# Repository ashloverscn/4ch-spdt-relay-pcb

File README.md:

# 4ch-spdt-relay-pcb
4ch-spdt-relay-pcb

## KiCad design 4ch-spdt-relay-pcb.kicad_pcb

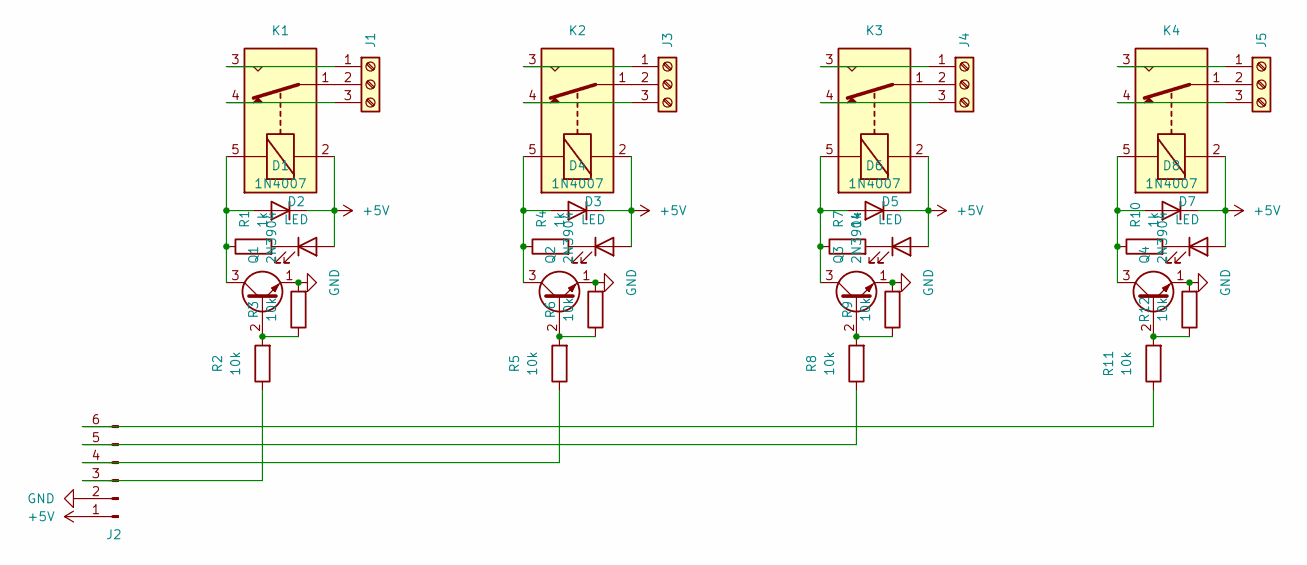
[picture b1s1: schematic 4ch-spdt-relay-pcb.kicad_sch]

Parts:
D1, D4, D6, D8: 1N4007; D_DO-41_SOD81_P10.16mm_Horizontal
D2, D3, D5, D7: LED; LED_D5.0mm
J1, J3, J4, J5: Screw_Terminal_01x03; TerminalBlock_Phoenix_MKDS-1,5-3-5.08_1x03_P5.08mm_Horizont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
J2: Conn_01x06_Pin; PinHeader_1x06_P2.54mm_Vertical
K1, K2, K3, K4: G5LE-1; Relay_SPDT_Omron-G5LE-1
Q1, Q2, Q3, Q4: 2N3904; TO-92_Inline
R1, R4, R7, R10: 1k; R_Axial_DIN0204_L3.6mm_D1.6mm_P2.54mm_Vertical
R2, R3, R5, R6, R8, R9, R11, R12: 10k; R_Axial_DIN0204_L3.6mm_D1.6mm_P2.54mm_Vertical

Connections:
+5V: D1.1 (K), D2.2 (A), D3.2 (A), D4.1 (K), D5.2 (A), D6.1 (K), D7.2 (A), D8.1 (K), J2.1, K1.2, K2.2, K3.2, K4.2
GND: J2.2, Q1.1 (E), Q2.1 (E), Q3.1 (E), Q4.1 (E), R3.2, R6.2, R9.2, R12.2
unnamed: D1.2 (A), K1.5, Q1.3 (C), R1.1
unnamed: D2.1 (K), R1.2
unnamed: D3.1 (K), R4.2
unnamed: D4.2 (A), K2.5, Q2.3 (C), R4.1
unnamed: D5.1 (K), R7.2
unnamed: D6.2 (A), K3.5, Q3.3 (C), R7.1
unnamed: D7.1 (K), R10.2
unnamed: D8.2 (A), K4.5, Q4.3 (C), R10.1
unnamed: J1.1, K1.3
unnamed: J1.2, K1.1
unnamed: J1.3, K1.4
unnamed: J2.3, R2.1
unnamed: J2.4, R5.1
unnamed: J2.5, R8.1
unnamed: J2.6, R11.1
unnamed: J3.1, K2.3
unnamed: J3.2, K2.1
unnamed: J3.3, K2.4
unnamed: J4.1, K3.3
unnamed: J4.2, K3.1
unnamed: J4.3, K3.4
unnamed: J5.1, K4.3
unnamed: J5.2, K4.1
unnamed: J5.3, K4.4
unnamed: Q1.2 (B), R2.2, R3.1
unnamed: Q2.2 (B), R5.2, R6.1
unnamed: Q3.2 (B), R8.2, R9.1
unnamed: Q4.2 (B), R11.2, R12.1

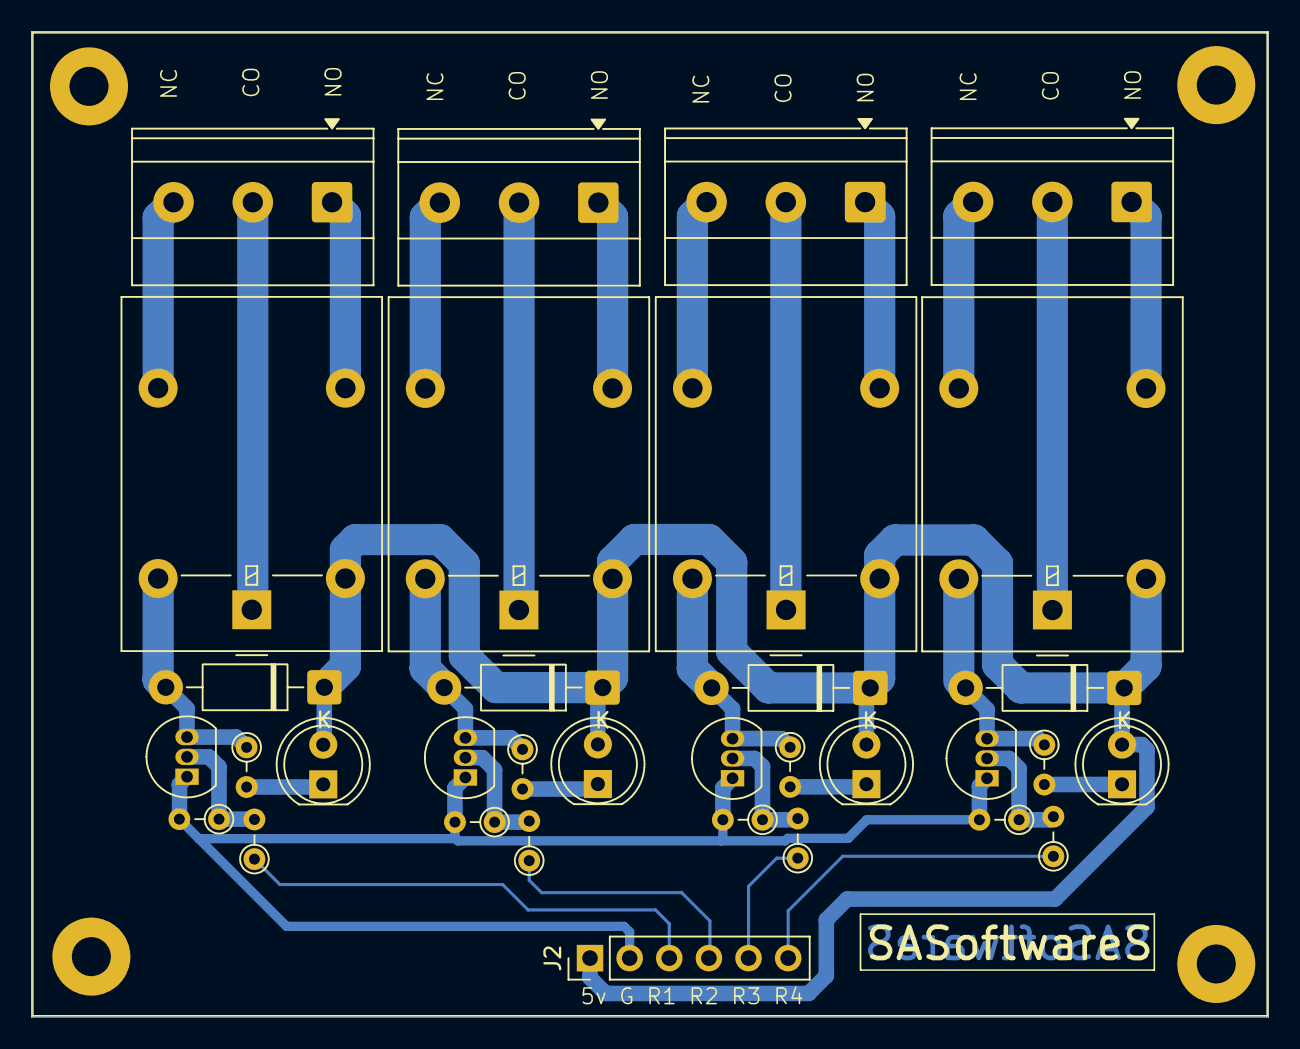
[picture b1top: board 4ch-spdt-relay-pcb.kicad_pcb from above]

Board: 2 copper layers, 79.3 x 63.1 mm, 33 parts (0 on the bottom side), 30 nets.
